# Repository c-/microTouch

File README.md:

# microTouch

Compact 3D printer bed probe based (very) loosely on the
[TinyTouch NMPG](https://www.thingiverse.com/thing:4661556).

I designed and built the first prototype a couple years ago. The current
version has been running since (approximately) May 2022 and has been
quite reliable, with only one misfire that I can remember.

# Design

It uses the same nano servo and a gravity based deployment as the
TT NMPG just started as a project to build a smaller TT PCB, but I've
changed it up to use a hall effect sensor with a small magnet embedded
in the slider, which allows for an even more compact package. I've also
changed the connector to a PH 2.0 and removed the servo connector
completely, soldering it directly to the PCB.

The size of the PCB is approximately 35mm x 25mm, and the shell will add
another 10mm or so. It should comfortably fit in the space needed by
a BLTouch.

I think there's room to crunch the design down even smaller, but I'm not
sure there's any need for a nanoTouch.

# Bill Of Materials

There's an [Interactive BOM](bom/ibom.html) for the electronics.

 * Nano linear servo (RH only). In theory you could use a LH version, but you'd
need to flip the mirror *everything*, including the hall sensor and magnet.
I haven't tested that.
 * A3144 hall effect sensor. This is an obsolete part, but it's still
available.
 * JST PH 2.0 connector. You can use a four or five pin, depending on
whether you need a different voltage for the signal than what the servo
uses (i.e. servo is 5V, signal might be 3.3V). If you use the 5 pin version
then you'll need to cut the solder jumper on the back.
 * 10uF, 100nF 0805 capacitors
 * 4.7K 0805 resistors
 * 0805 red LED (other colors probably work, but I've only tested red)
 * 3x2mm rare earth magnet

You'll need a PCB. It *can* be homemade (I made the first version on a PCB
mill), but you'll have a battle with the servo pads. I ordered my finished
versions [from Oshpark](https://oshpark.com/shared_projects/54oETibN),
and you can't really beat the price for something that small.

You'll need printed parts. Minimally the slider and the cover, and I found
a backer/spacer necessary, but you might need to design a different way to
mount to your printer.  I printed the slider with
[Igus iglide I150-PF](https://www.igus.com/product/12404),
but probably anything would work okay. The slider and the body need to be
sanded to ensure smooth deployment, and getting that right is by far the
most finicky part of the job. You'll probably have to drill the slider hole
larger to hold the magnet (a press fit is enough).

For the probe itself I use a M3 bolt (25mm, I think?), but anything you can
thread into the slider body should be fine as long as it has some weight to
it. The bolt can be threaded in quite far and is the main way to adjust
the position of the problem, along with the servo angles.

# Assembly

Remove the wires from the servo.

Do this by scraping away the glue at the PCB, then desolder the wires and
touch up the pads with fresh solder. Don't overbuild solder on the pads,
they should be somewhat flat.

Solder the components. See the Interactive bom for details of what goes
where. Do the surface mount components first or you'll find things get
cramped. The hall sensor should be mounted a bit off the board, just below
where the slider will clear it.

Attach the servo.

I used tiny eyeglass screws (I want to say 1mm) without bothering to thread
anything. At the back, the wire pads on the servo should align
with the three
[castellated pads](https://docs.oshpark.com/tips+tricks/castellation/).

Solder the servo pads to the castellanations. This is done by stabbing the
iron tip down so it's touching both the pad and the side of the
catellanation, and wicking solder from the top. A fine tip and small
diameter solder would be good for this, and you don't need much solder.

With the PCB done, it's time to assemble everything else. It's not a bad
idea to thread the mounting hole for M3 now, but it's probably not
necessary.  Insert the
slider, screw in the plunger, and the PCB should just press in from the
back.

This would be a good time to run a test before installing it. I use an
Arduino Nano (there's a test script) to run it through its paces. In
particular, you might have to flip the magnet and give the hall sensor a
slight bend in one direction or another. Take note of the deploy/stow
angles for your firmware configuration.

Then attach it to your printer. Mine is attached through a hole in the back
of my X carriage.

In hindsight, I probably could have put the connector on the other side.

# Configuration

At the configuration level, it's just your average servo-based probe.
Depending on your servo, polishing, and assembly you *might* not be
able to use the full 180 degree range of the servo due to binding,
but you can still easily achieve a 5mm range between stowed and deployed.

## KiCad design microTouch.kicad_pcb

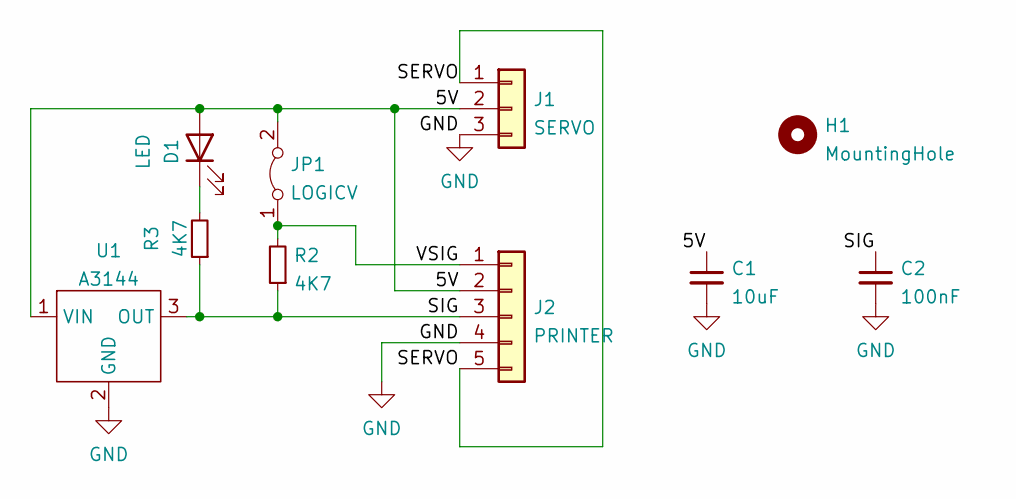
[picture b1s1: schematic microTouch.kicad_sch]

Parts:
C1: 10uF; C_0805_2012Metric_Pad1.18x1.45mm_HandSolder
C2: 100nF; C_0805_2012Metric_Pad1.18x1.45mm_HandSolder
D1: LED; LED_0805_2012Metric_Pad1.15x1.40mm_HandSolder
H1: MountingHole; MountingHole_3.2mm_M3
J1: SERVO; GS-1502
J2: PRINTER; JST_PH_B5B-PH-K_1x05_P2.00mm_Vertical
JP1: LOGICV; SolderJumper-2_P1.3mm_Bridged_RoundedPad1.0x1.5mm
R2, R3: 4K7; R_0805_2012Metric_Pad1.20x1.40mm_HandSolder
U1: A3144; TO-92Flat

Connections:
/5V: C1.1, D1.2 (A), J1.2, J2.2, JP1.2 (B), U1.1 (VIN)
/SERVO: J1.1, J2.5
/SIG: C2.1, J2.3, R2.1, R3.1, U1.3 (OUT)
/VSIG: J2.1, JP1.1 (A), R2.2
GND: C1.2, C2.2, J1.3, J2.4, U1.2 (GND)
unnamed: D1.1 (K), R3.2

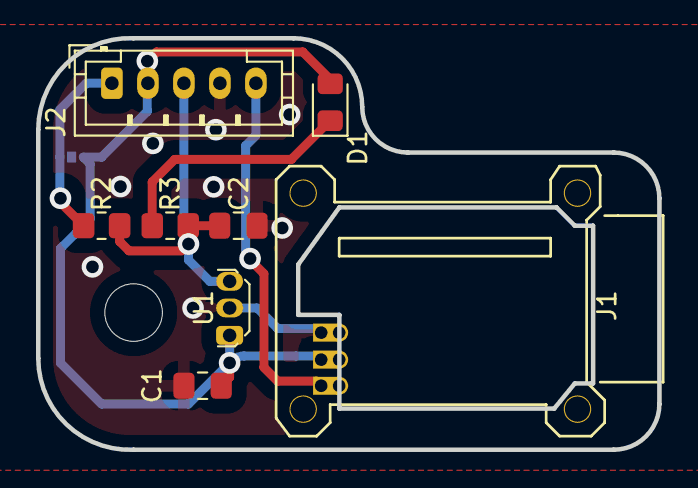
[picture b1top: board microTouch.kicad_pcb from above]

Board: 2 copper layers, 34.5 x 22.9 mm, 10 parts (1 on the bottom side), 6 nets.

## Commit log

2023-04-06 fix photint pinout, adjust pullup, move LED out further
2023-04-06 PCB first rev
2023-04-06 more model work
2023-04-06 small refinements, but good enough
2023-04-06 add BOM
2023-04-06 smaller
2023-04-06 almost there with model
2023-04-06 more minor tweaks
2023-04-06 assorted tweaks
2023-04-06 more tweaking and cleanups
2023-04-06 redesign with a A3144 hall effect sensor
2023-04-06 adjust flag for a greater range between stowed and triggered
2023-04-06 whole bunch of tweaks to match the board, cleanup the layout
2023-04-06 update BOM
2023-04-06 need some kind of backer/spacer plate when mounting to a flat surface
2023-04-06 more cover refinements
2023-04-06 use a tab for the screw
2023-04-06 a few more model tweaks
2023-04-06 forgot to label the bins in the silk screen
2023-04-06 a few more layout tweaks
2023-04-06 fix up the model a bit
2023-04-06 move some stuff around, add some filter caps for noise
2023-04-06 small stuff
2023-04-06 thicker backer
2023-04-06 some adjustments against a real board
2023-04-06 redo the track rounding
2023-04-06 missed a file
2023-04-06 ibom
2023-04-06 more model tweaks
2023-04-06 write the fine manual
2023-04-06 actually write the fine manual
2023-04-06 minor tweaks
2023-04-06 cleaning up
2023-04-07 forgot to mention the magnet
2023-04-07 a note on testing
